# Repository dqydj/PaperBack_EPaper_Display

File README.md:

# PaperBack EPaper Display

PaperBack is a modular, internet connected _*OR*_ VGA EPaper Display. It consists of a breakout board for a 39 pin ePaper display and an ESP32 in one mode. In the other, remove the ESP32 and attach a VGA Conversion board and use regular VGA input to drive the display!

PaperBack is an entry in the 2017 Hackaday Prize, you can see a more complete (and verbose!) [writeup here](https://hackaday.io/project/21607-paperback-desktop-e-paper-monitor).

## Hardware Overview

Currently, PaperBack works both driven by an ESP32 Development Board, or directly via VGA with the attached second PCB.

Hardware Overview:

* Espressif ESP32 Dev Board
* ED060SC4 // LB060S01 // LB060S04 6" ePaper Display
* 800x600 Resolution
* 16 Color (Greyscale) Support / 4-Bit Grey

## Software/Firmware Overview

Remember, choose one at a time! You can use the ESP32 breakout board with the ESP32 dev board, or remove the dev board and attach the VGA converter.

### VGA Driven

Unplug any ESP32 from the socket and attach both boards, then attach power (see below). When the board detects a signal it will start to refresh.

All firmware is in the /firmware_VGA/FPGA and /firmware_VGA/Microcontroller directories.

The user switches change color depth (read: shades of gray. 2 color is black & white.) and refresh speed:
Switch 3 (Furthest from Microcontroller)
Switch 2
Switch 1 (Closest to Microcontroller)

* On  On  On  - 16 color, ~10 seconds between frames
* On  On  Off - 16 color, ~5 seconds between frames
* On  Off On  - 4 color, ~10 seconds between frames
* On  Off Off - 4 color, ~5 seconds between frames
* Off On  On  - 4 color, ~1 frame per second
* Off On  Off - 2 color, ~10 seconds between frames
* Off Off On  - 2 color, ~5 seconds between frames
* Off Off Off - 2 color, ~1 frame per second

### ESP32 Dev Board Driven

Remove the second PCB if attached, then add the ESP32. There are *easy* ways to add power (there are pins exposed too, but these are easiest). Unless using Lithium and the DC adapter, only use one at a time!
* The board supports a single cell lithium ion battery with JST connector, and can charge it through the DC adapter hookup. Polarity is marker.
* The board can take a 2.1mm jack DC adapter, center positive. Aim for between 4.8 and 7 volts (don't create too much heat with something more).
* Disconnect all other supplies if you do this, but you can power it over USB from the ESP32. Connect the jumper labeled 'JP2' for this option.

Demos:

1. The Python utility `convert.py` in `/software/image_converter` automatically converts images which are compatible with Paperback's basic image demo. The image demo is in /firmware_ESP32/Paperback_Greyscale_Static_Image.

## Licensing and Other

* My main site: [DQYDJ](https://dqydj.com)
* Where available, all of the code is licensed as MIT.
* Where available, all of the hardware is licensed as MIT.
* If needed, other licenses will be quoted for individual parts.
* I would, of course, _love_ a link if you use any assets - but feel free to use everything as you wish.

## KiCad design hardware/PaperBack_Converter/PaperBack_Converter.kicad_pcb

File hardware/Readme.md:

# Hardware Directory

Here you'll find the files you will need to reproduce Paperback.  There are two boards:

* *PaperBack_Display* The Display breakout board.  Can take an ESP32 Development Kit and run the display without the Video converter board.
* *PaperBack_Converter* The VGA conversion board.  Takes VGA, captures a frame, puts it in memory, then outputs to the ePaper screen.  _You can't run the ESP32 if you choose to dock board 2! Do not insert it!_.  

## Editing the Files

All files are from KiCad, although Gerbers are a universal format.  I've also included the PDF schematics as well if you'd like to spin a new PCB from scratch.

## License

MIT

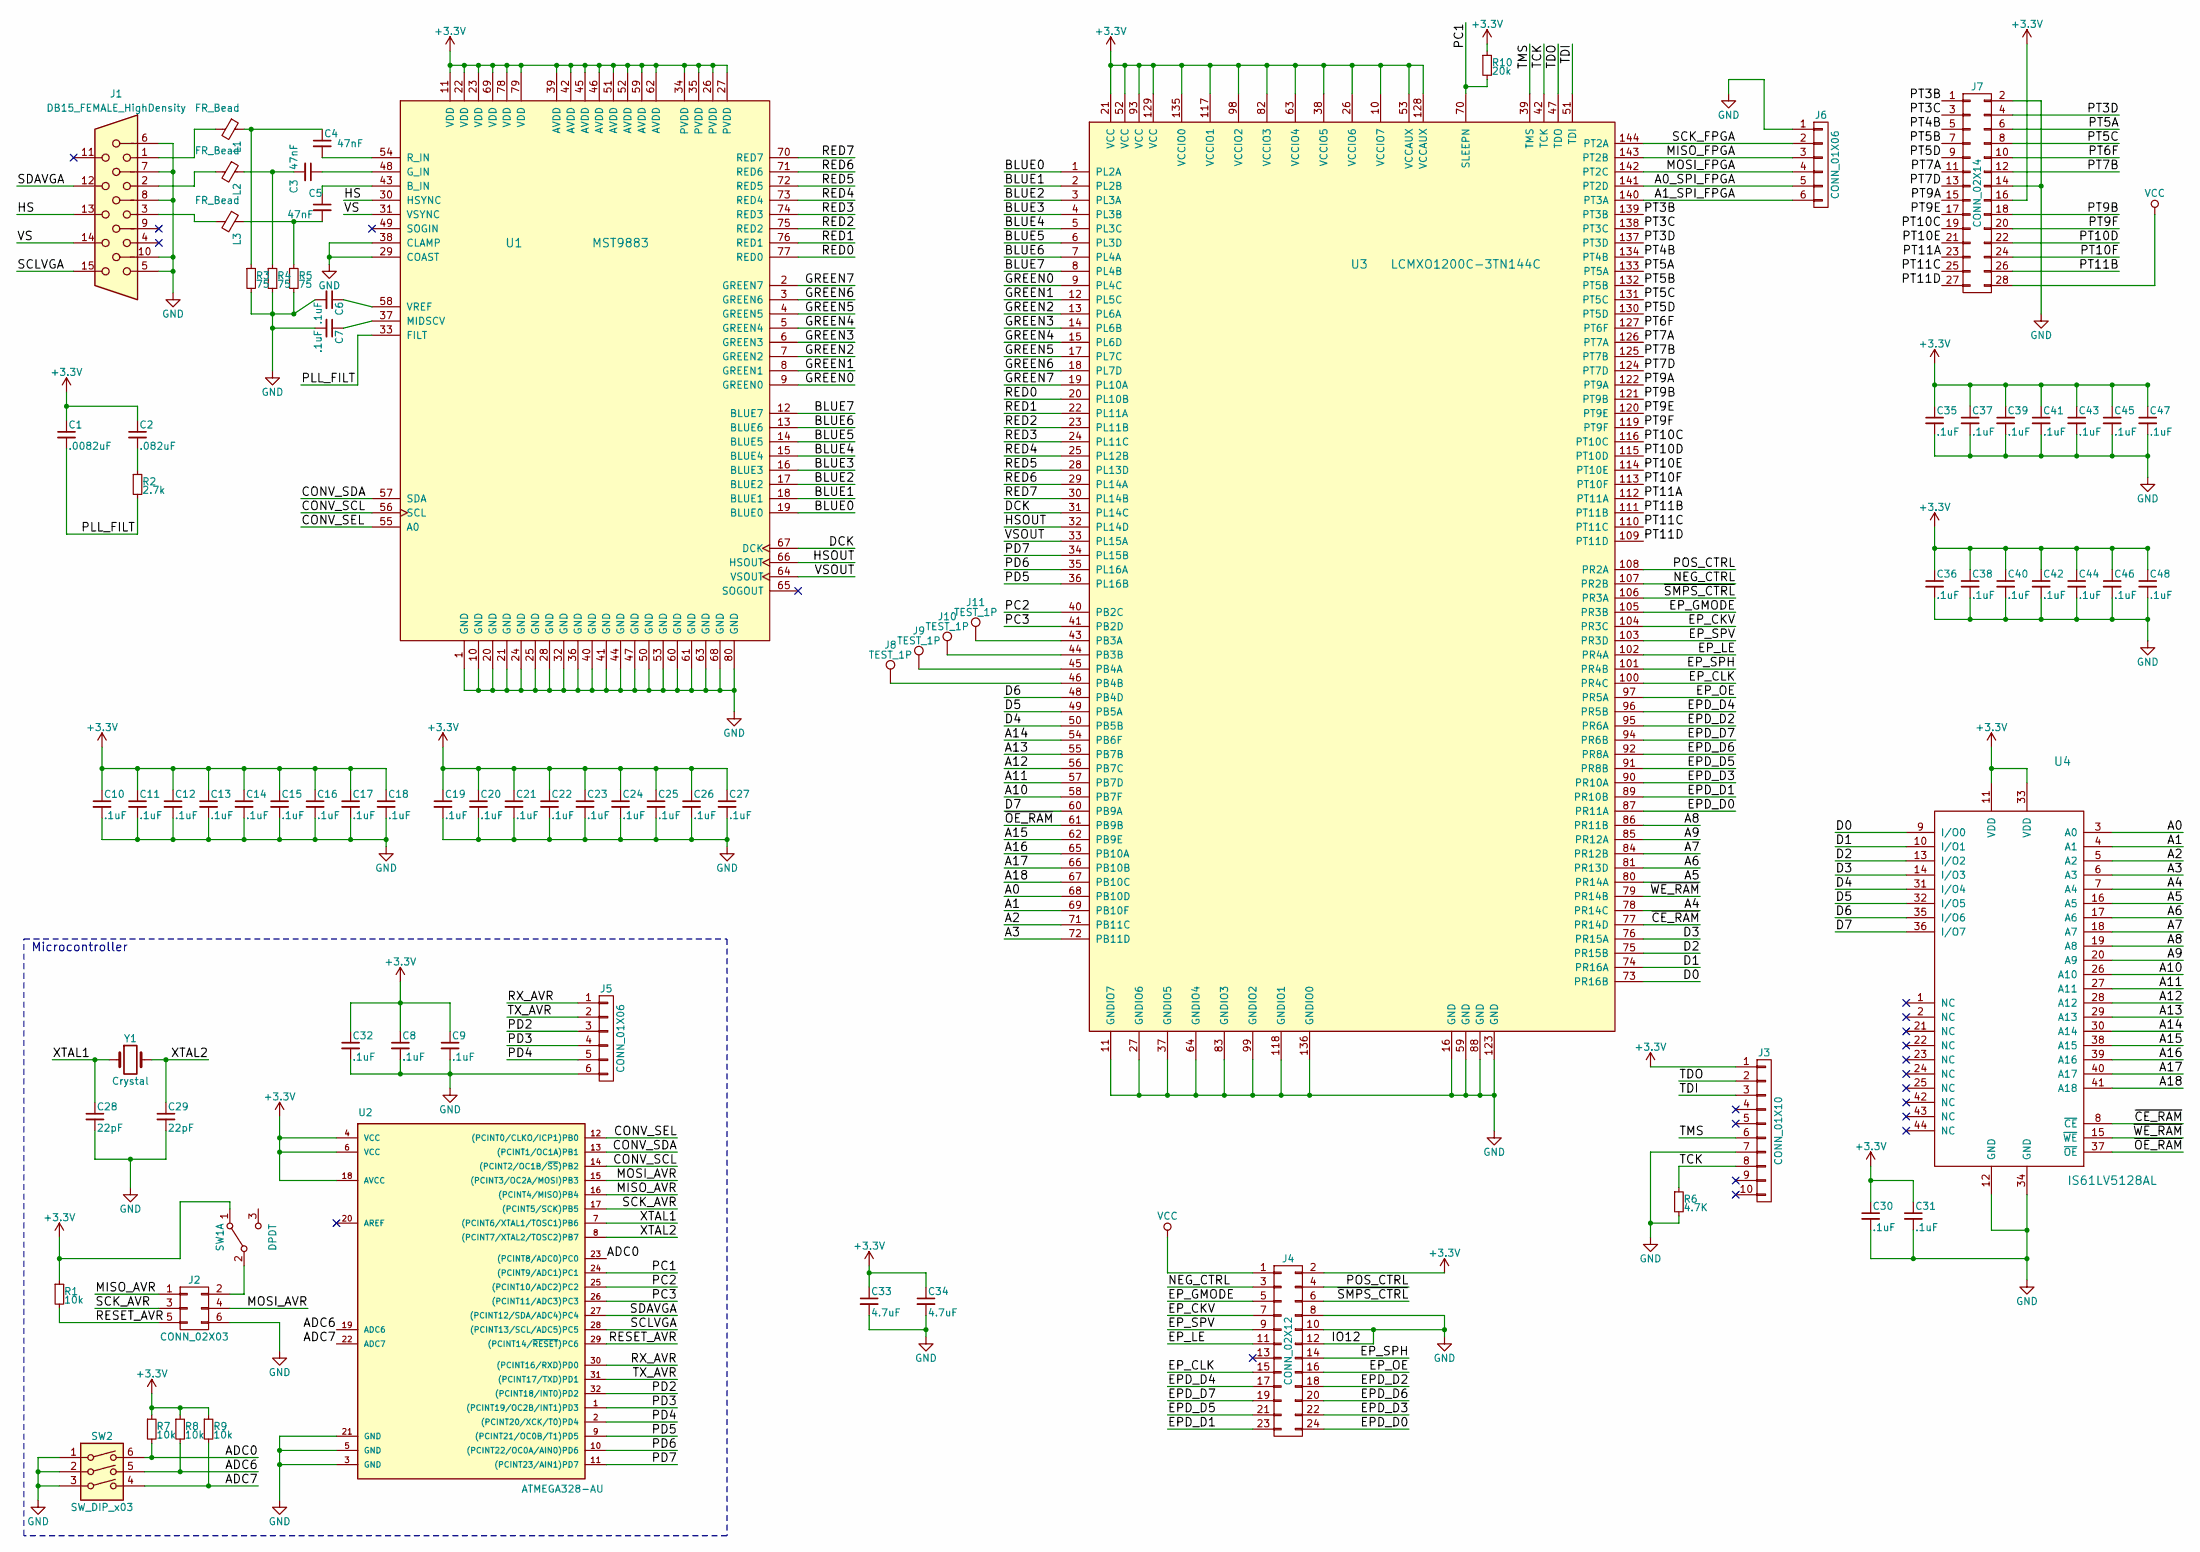
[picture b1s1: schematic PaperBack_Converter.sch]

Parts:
C1: .0082uF; C_0603_HandSoldering
C2: .082uF; C_0603_HandSoldering
C3, C4, C5: 47nF; C_0603_HandSoldering
C6, C7, C8, C9, C10, C11, C12, C13, C14, C15, C16, C17, C18, C19, C20, C21, C22, C23, C24, C25, C26, C27, C30, C31, C32, C35, C36, C37, C38, C39, C40, C41, C42, C43, C44, C45, C46, C47, C48: .1uF; C_0603_HandSoldering
C28, C29: 22pF; C_0603_HandSoldering
C33, C34: 4.7uF; C_0603_HandSoldering
J1: DB15_FEMALE_HighDensity; VGA_HD15
J2: CONN_02X03; Pin_Header_Straight_2x03_Pitch2.54mm
J3: CONN_01X10; Pin_Header_Straight_1x10_Pitch2.54mm
J4: CONN_02X12; Pin_Header_Straight_2x12_Pitch2.54mm
J5, J6: CONN_01X06; Pin_Header_Straight_1x06_Pitch2.54mm
J7: CONN_02X14; Socket_Strip_Straight_2x14_Pitch2.54mm
J8, J9, J10, J11: TEST_1P; Measurement_Point_Round-SMD-Pad_Small
L1, L2, L3: FR_Bead; L_0805_HandSoldering
R1, R7, R8, R9: 10k; R_0805_HandSoldering
R2: 2.7k; R_0805_HandSoldering
R3, R4, R5: 75; R_0805_HandSoldering
R6: 4.7K; R_0805_HandSoldering
R10: 20k; R_0805_HandSoldering
SW1: DPDT; Pin_Header_Straight_1x03_Pitch2.54mm
SW2: SW_DIP_x03; SW_DIP_x3_W7.62mm_Slide
U1: MST9883; TQFP-80_14x14mm_Pitch0.65mm
U2: ATMEGA328-AU; TQFP-32_7x7mm_Pitch0.8mm
U3: LCMXO1200C-3TN144C; TQFP-144_20x20mm_Pitch0.5mm
U4: IS61LV5128AL; TSOP_II_44_0.8mm
Y1: Crystal; Crystal_SMD_HC49-SD

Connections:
+3V3: C1.1, C2.1, C8.1, C9.1, C10.1, C11.1, C12.1, C13.1, C14.1, C15.1, C16.1, C17.1, C18.1, C19.1, C20.1, C21.1, C22.1, C23.1, C24.1, C25.1, C26.1, C27.1, C30.1, C31.1, C32.1, C33.1, C34.1, C35.1, C36.1, C37.1, C38.1, C39.1, C40.1, C41.1, C42.1, C43.1, C44.1, C45.1, C46.1, C47.1, C48.1, J3.1, J4.2, J7.16, R1.1, R7.1, R8.1, R9.1, R10.1, SW1.1 (A), U1.11 (VDD), U1.22 (VDD), U1.23 (VDD), U1.26 (PVDD), U1.27 (PVDD), U1.34 (PVDD), U1.35 (PVDD), U1.39 (AVDD), U1.42 (AVDD), U1.45 (AVDD), U1.46 (AVDD), U1.51 (AVDD), U1.52 (AVDD), U1.59 (AVDD), U1.62 (AVDD), U1.69 (VDD), U1.78 (VDD), U1.79 (VDD), U2.4 (VCC), U2.6 (VCC), U2.18 (AVCC), U3.10 (VCCIO7), U3.21 (VCC), U3.26 (VCCIO6), U3.38 (VCCIO5), U3.52 (VCC), U3.53 (VCCAUX), U3.63 (VCCIO4), U3.82 (VCCIO3), U3.93 (VCC), U3.98 (VCCIO2), U3.117 (VCCIO1), U3.128 (VCCAUX), U3.129 (VCC), U3.135 (VCCIO0), U4.11 (VDD), U4.33 (VDD)
/A0: U3.68 (PB10D), U4.3 (A0)
/A0_SPI_FPGA: J6.5, U3.141 (PT2D)
/A1: U3.69 (PB10F), U4.4 (A1)
/A1_SPI_FPGA: J6.6, U3.140 (PT3A)
/A2: U3.71 (PB11C), U4.5 (A2)
/A3: U3.72 (PB11D), U4.6 (A3)
/A4: U3.78 (PR14C), U4.7 (A4)
/A5: U3.80 (PR14A), U4.16 (A5)
/A6: U3.81 (PR13D), U4.17 (A6)
/A7: U3.84 (PR12B), U4.18 (A7)
/A8: U3.86 (PR11B), U4.19 (A8)
/A9: U3.85 (PR12A), U4.20 (A9)
/A10: U3.58 (PB7F), U4.26 (A10)
/A11: U3.57 (PB7D), U4.27 (A11)
/A12: U3.56 (PB7C), U4.28 (A12)
/A13: U3.55 (PB7B), U4.29 (A13)
/A14: U3.54 (PB6F), U4.30 (A14)
/A15: U3.62 (PB9E), U4.38 (A15)
/A16: U3.65 (PB10A), U4.39 (A16)
/A17: U3.66 (PB10B), U4.40 (A17)
/A18: U3.67 (PB10C), U4.41 (A18)
/ADC0: R7.2, SW2.6, U2.23 ((PCINT8/ADC0)PC0)
/ADC6: R8.2, SW2.5, U2.19 (ADC6)
/ADC7: R9.2, SW2.4, U2.22 (ADC7)
/BLUE0: U1.19 (BLUE0), U3.1 (PL2A)
/BLUE1: U1.18 (BLUE1), U3.2 (PL2B)
/BLUE2: U1.17 (BLUE2), U3.3 (PL3A)
/BLUE3: U1.16 (BLUE3), U3.4 (PL3B)
/BLUE4: U1.15 (BLUE4), U3.5 (PL3C)
/BLUE5: U1.14 (BLUE5), U3.6 (PL3D)
/BLUE6: U1.13 (BLUE6), U3.7 (PL4A)
/BLUE7: U1.12 (BLUE7), U3.8 (PL4B)
/CONV_SCL: U1.56 (SCL), U2.14 ((PCINT2/OC1B/~SS~)PB2)
/CONV_SDA: U1.57 (SDA), U2.13 ((PCINT1/OC1A)PB1)
/CONV_SEL: U1.55 (A0), U2.12 ((PCINT0/CLKO/ICP1)PB0)
/D0: U3.73 (PR16B), U4.9 (I/O0)
/D1: U3.74 (PR16A), U4.10 (I/O1)
/D2: U3.75 (PR15B), U4.13 (I/O2)
/D3: U3.76 (PR15A), U4.14 (I/O3)
/D4: U3.50 (PB5B), U4.31 (I/O4)
/D5: U3.49 (PB5A), U4.32 (I/O5)
/D6: U3.48 (PB4D), U4.35 (I/O6)
/D7: U3.60 (PB9A), U4.36 (I/O7)
/DCK: U1.67 (DCK), U3.31 (PL14C)
/EPD_D0: J4.24, U3.87 (PR11A)
/EPD_D1: J4.23, U3.89 (PR10B)
/EPD_D2: J4.18, U3.95 (PR6A)
/EPD_D3: J4.22, U3.90 (PR10A)
/EPD_D4: J4.17, U3.96 (PR5B)
/EPD_D5: J4.21, U3.91 (PR8B)
/EPD_D6: J4.20, U3.92 (PR8A)
/EPD_D7: J4.19, U3.94 (PR6B)
/EP_CKV: J4.7, U3.104 (PR3C)
/EP_CLK: J4.15, U3.100 (PR4C)
/EP_GMODE: J4.5, U3.105 (PR3B)
/EP_LE: J4.11, U3.102 (PR4A)
/EP_OE: J4.16, U3.97 (PR5A)
/EP_SPH: J4.14, U3.101 (PR4B)
/EP_SPV: J4.9, U3.103 (PR3D)
/GREEN0: U1.9 (GREEN0), U3.9 (PL4C)
/GREEN1: U1.8 (GREEN1), U3.12 (PL5C)
/GREEN2: U1.7 (GREEN2), U3.13 (PL6A)
/GREEN3: U1.6 (GREEN3), U3.14 (PL6B)
/GREEN4: U1.5 (GREEN4), U3.15 (PL6D)
/GREEN5: U1.4 (GREEN5), U3.17 (PL7C)
/GREEN6: U1.3 (GREEN6), U3.18 (PL7D)
/GREEN7: U1.2 (GREEN7), U3.19 (PL10A)
/HS: J1.13, U1.30 (HSYNC)
/HSOUT: U1.66 (HSOUT), U3.32 (PL14D)
/MISO_AVR: J2.1, U2.16 ((PCINT4/MISO)PB4)
/MISO_FPGA: J6.3, U3.143 (PT2B)
/MOSI_AVR: J2.4, U2.15 ((PCINT3/OC2A/MOSI)PB3)
/MOSI_FPGA: J6.4, U3.142 (PT2C)
/NEG_CTRL: J4.3, U3.107 (PR2B)
/PC1: R10.2, U2.24 ((PCINT9/ADC1)PC1), U3.70 (SLEEPN)
/PC2: U2.25 ((PCINT10/ADC2)PC2), U3.40 (PB2C)
/PC3: U2.26 ((PCINT11/ADC3)PC3), U3.41 (PB2D)
/PD2: J5.3, U2.32 ((PCINT18/INT0)PD2)
/PD3: J5.4, U2.1 ((PCINT19/OC2B/INT1)PD3)
/PD4: J5.5, U2.2 ((PCINT20/XCK/T0)PD4)
/PD5: U2.9 ((PCINT21/OC0B/T1)PD5), U3.36 (PL16B)
/PD6: U2.10 ((PCINT22/OC0A/AIN0)PD6), U3.35 (PL16A)
/PD7: U2.11 ((PCINT23/AIN1)PD7), U3.34 (PL15B)
/PLL_FILT: C1.2, R2.2, U1.33 (FILT)
/POS_CTRL: J4.4, U3.108 (PR2A)
/PT3B: J7.1, U3.139 (PT3B)
/PT3C: J7.3, U3.138 (PT3C)
/PT3D: J7.4, U3.137 (PT3D)
/PT4B: J7.5, U3.134 (PT4B)
/PT5A: J7.6, U3.133 (PT5A)
/PT5B: J7.7, U3.132 (PT5B)
/PT5C: J7.8, U3.131 (PT5C)
/PT5D: J7.9, U3.130 (PT5D)
/PT6F: J7.10, U3.127 (PT6F)
/PT7A: J7.11, U3.126 (PT7A)
/PT7B: J7.12, U3.125 (PT7B)
/PT7D: J7.13, U3.124 (PT7D)
/PT9A: J7.15, U3.122 (PT9A)
/PT9B: J7.18, U3.121 (PT9B)
/PT9E: J7.17, U3.120 (PT9E)
/PT9F: J7.20, U3.119 (PT9F)
/PT10C: J7.19, U3.116 (PT10C)
/PT10D: J7.22, U3.115 (PT10D)
/PT10E: J7.21, U3.114 (PT10E)
/PT10F: J7.24, U3.113 (PT10F)
/PT11A: J7.23, U3.112 (PT11A)
/PT11B: J7.26, U3.111 (PT11B)
/PT11C: J7.25, U3.110 (PT11C)
/PT11D: J7.27, U3.109 (PT11D)
/RED0: U1.77 (RED0), U3.20 (PL10B)
/RED1: U1.76 (RED1), U3.22 (PL11A)
/RED2: U1.75 (RED2), U3.23 (PL11B)
/RED3: U1.74 (RED3), U3.24 (PL11C)
/RED4: U1.73 (RED4), U3.25 (PL12B)
/RED5: U1.72 (RED5), U3.28 (PL13D)
/RED6: U1.71 (RED6), U3.29 (PL14A)
/RED7: U1.70 (RED7), U3.30 (PL14B)
/RESET_AVR: J2.5, R1.2, U2.29 ((PCINT14/~RESET~)PC6)
/RX_AVR: J5.1, U2.30 ((PCINT16/RXD)PD0)
/SCK_AVR: J2.3, U2.17 ((PCINT5/SCK)PB5)
/SCK_FPGA: J6.2, U3.144 (PT2A)
/SCLVGA: J1.15, U2.28 ((PCINT13/SCL/ADC5)PC5)
/SDAVGA: J1.12, U2.27 ((PCINT12/SDA/ADC4)PC4)
/TCK: J3.8, R6.1, U3.42 (TCK)
/TDI: J3.3, U3.51 (TDI)
/TDO: J3.2, U3.47 (TDO)
/TMS: J3.6, U3.39 (TMS)
/TX_AVR: J5.2, U2.31 ((PCINT17/TXD)PD1)
/VS: J1.14, U1.31 (VSYNC)
/VSOUT: U1.64 (VSOUT), U3.33 (PL15A)
/XTAL1: C28.1, U2.7 ((PCINT6/XTAL1/TOSC1)PB6), Y1.1
/XTAL2: C29.1, U2.8 ((PCINT7/XTAL2/TOSC2)PB7), Y1.2
/~CE_RAM: U3.77 (PR14D), U4.8 (~CE)
/~OE_RAM: U3.61 (PB9B), U4.37 (~OE)
/~SMPS_CTRL: J4.6, U3.106 (PR3A)
/~WE_RAM: U3.79 (PR14B), U4.15 (~WE)
GND: C6.2, C7.2, C8.2, C9.2, C10.2, C11.2, C12.2, C13.2, C14.2, C15.2, C16.2, C17.2, C18.2, C19.2, C20.2, C21.2, C22.2, C23.2, C24.2, C25.2, C26.2, C27.2, C28.2, C29.2, C30.2, C31.2, C32.2, C33.2, C34.2, C35.2, C36.2, C37.2, C38.2, C39.2, C40.2, C41.2, C42.2, C43.2, C44.2, C45.2, C46.2, C47.2, C48.2, J1.5, J1.6, J1.7, J1.8, J1.10, J2.6, J3.7, J4.8, J4.10, J4.12, J5.6, J6.1, J7.2, J7.14, R3.2, R4.2, R5.2, R6.2, SW2.1, SW2.2, SW2.3, U1.1 (GND), U1.10 (GND), U1.20 (GND), U1.21 (GND), U1.24 (GND), U1.25 (GND), U1.28 (GND), U1.29 (COAST), U1.32 (GND), U1.36 (GND), U1.38 (CLAMP), U1.40 (GND), U1.41 (GND), U1.44 (GND), U1.47 (GND), U1.50 (GND), U1.53 (GND), U1.60 (GND), U1.61 (GND), U1.63 (GND), U1.68 (GND), U1.80 (GND), U2.3 (GND), U2.5 (GND), U2.21 (GND), U3.11 (GNDIO7), U3.16 (GND), U3.27 (GNDIO6), U3.37 (GNDIO5), U3.59 (GND), U3.64 (GNDIO4), U3.83 (GNDIO3), U3.88 (GND), U3.99 (GNDIO2), U3.118 (GNDIO1), U3.123 (GND), U3.136 (GNDIO0), U4.12 (GND), U4.34 (GND)
unnamed: C2.2, R2.1
unnamed: C3.1, U1.48 (G_IN)
unnamed: C3.2, L2.1, R4.1
unnamed: C4.1, L1.1, R3.1
unnamed: C4.2, U1.54 (R_IN)
unnamed: C5.1, U1.43 (B_IN)
unnamed: C5.2, L3.1, R5.1
unnamed: C6.1, U1.58 (VREF)
unnamed: C7.1, U1.37 (MIDSCV)
unnamed: J1.1, L1.2
unnamed: J1.2, L2.2
unnamed: J1.3, L3.2
unnamed: J2.2, SW1.2 (B)
unnamed: J8.1, U3.46 (PB4B)
unnamed: J9.1, U3.45 (PB4A)
unnamed: J10.1, U3.44 (PB3B)
unnamed: J11.1, U3.43 (PB3A)
VCC: J4.1, J7.28

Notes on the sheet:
Microcontroller

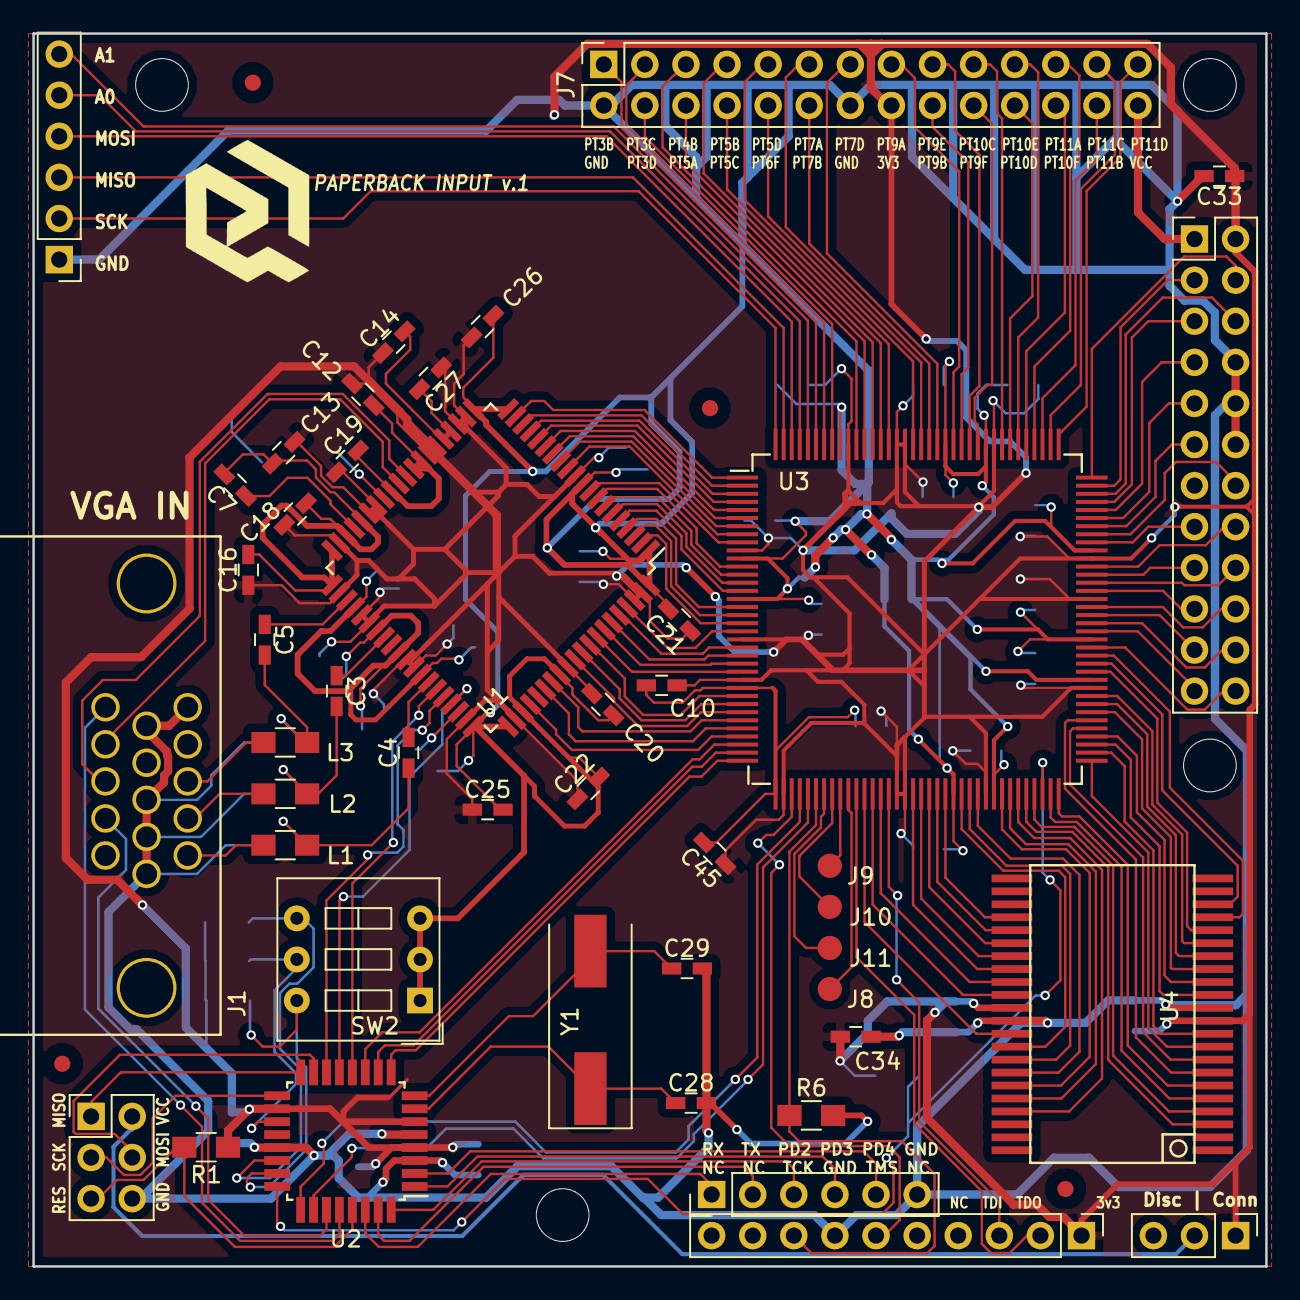
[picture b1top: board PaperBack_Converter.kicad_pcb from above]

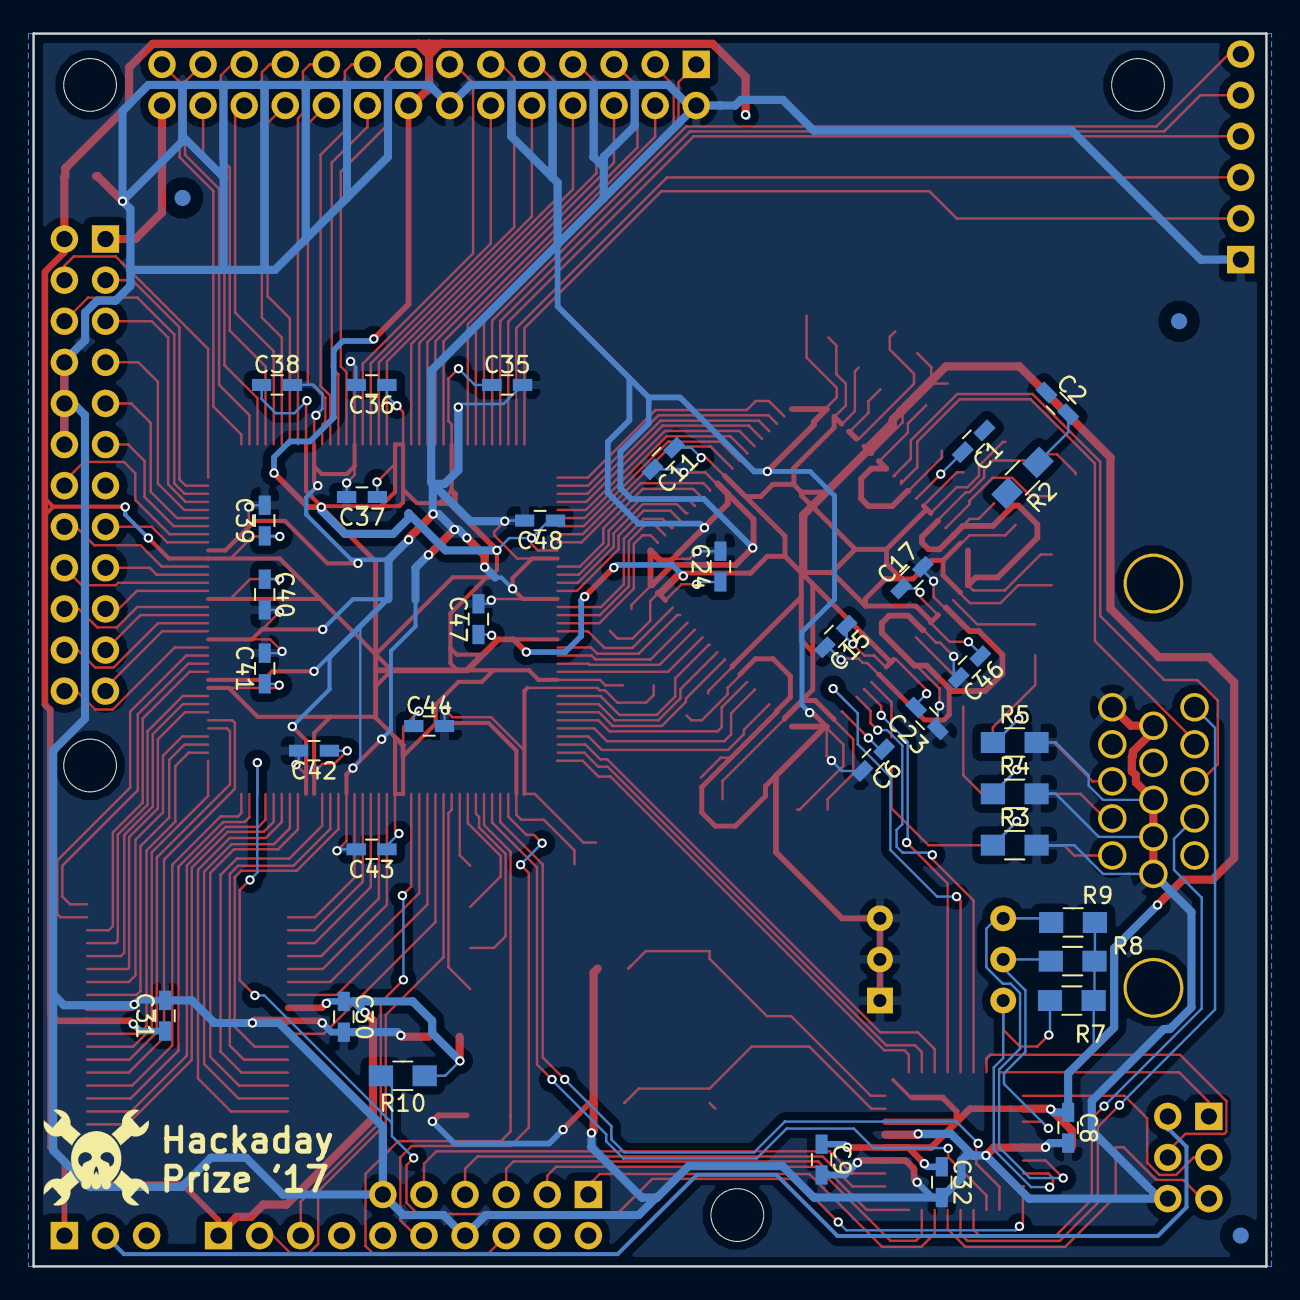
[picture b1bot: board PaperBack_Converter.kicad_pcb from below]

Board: 2 copper layers, 76.2 x 76.2 mm, 79 parts (34 on the bottom side), 156 nets.

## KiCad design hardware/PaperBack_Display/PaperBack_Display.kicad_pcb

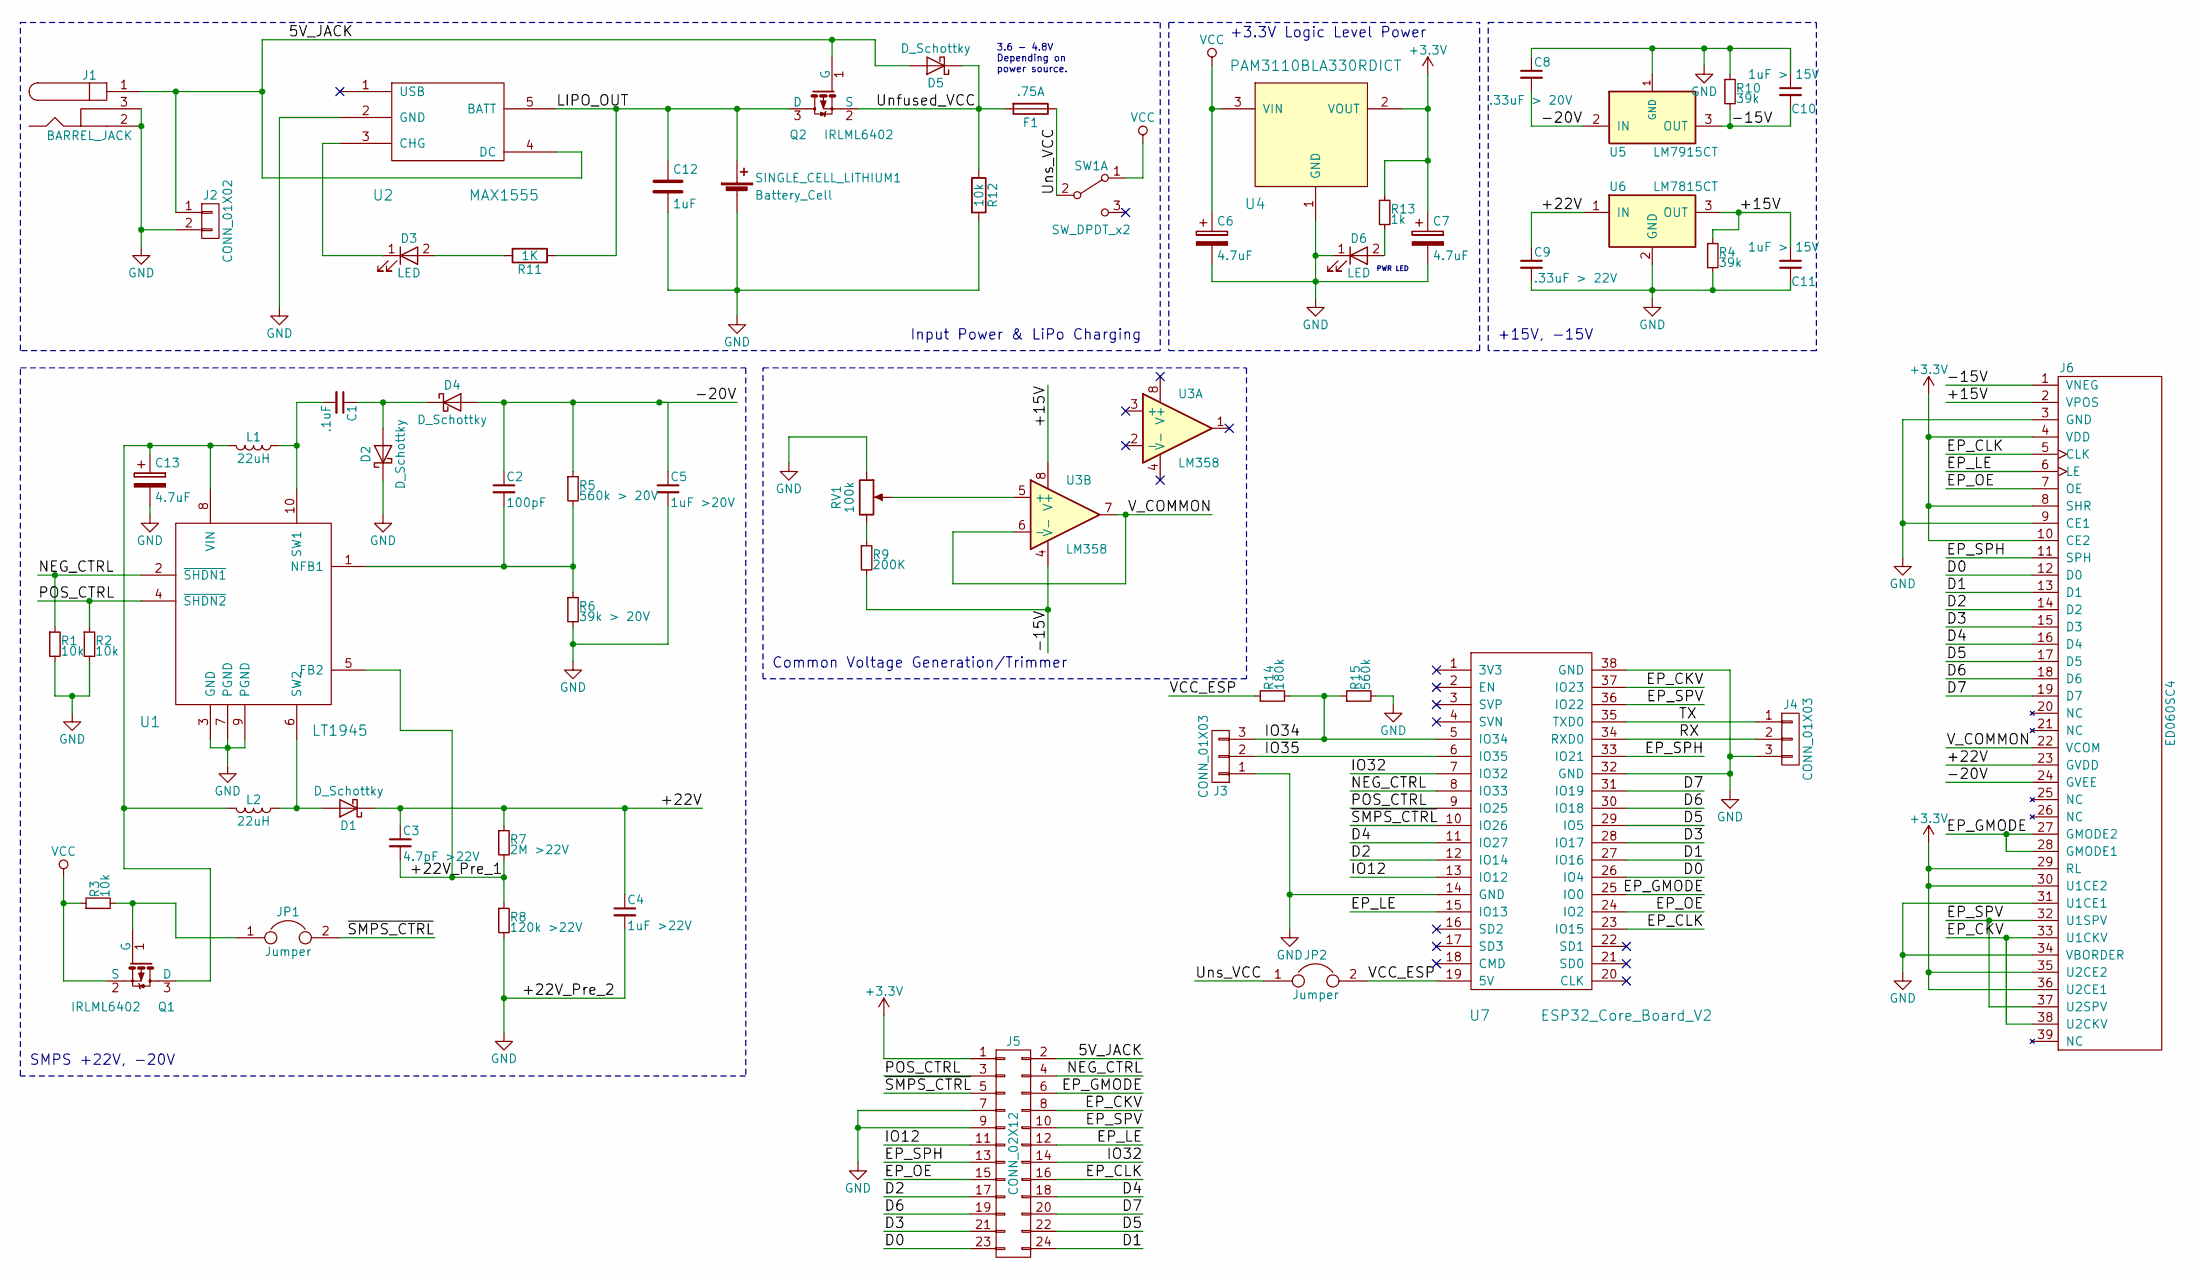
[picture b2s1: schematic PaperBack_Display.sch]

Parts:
C1: .1uF; C_0603_HandSoldering
C2: 100pF; C_0603_HandSoldering
C3: 4.7pF >22V; C_0603_HandSoldering
C4: 1uF >22V; C_0603_HandSoldering
C5: 1uF >20V; C_0603_HandSoldering
C6, C7, C13: 4.7uF; C_0603_HandSoldering
C8: .33uF > 20V; C_0603_HandSoldering
C9: .33uF > 22V; C_0603_HandSoldering
C10, C11: 1uF > 15V; C_0603_HandSoldering
C12: 1uF; C_0603_HandSoldering
D1, D2, D4, D5: D_Schottky; D_SOD-123F
D3, D6: LED; LED_0805
F1: .75A; R_1210_HandSoldering
J1: BARREL_JACK; Switchcraft_5.5_2.1_Barrel_Jack
J2: CONN_01X02; Pin_Header_Straight_1x02_Pitch2.54mm
J3, J4: CONN_01X03; Pin_Header_Straight_1x03_Pitch2.54mm
J5: CONN_02X12; Pin_Header_Straight_2x12_Pitch2.54mm
J6: ED060SC4
JP1, JP2: Jumper; Pin_Header_Straight_1x02_Pitch2.54mm
L1, L2: 22uH; DG6050C_Murata_Inductor
Q1, Q2: IRLML6402; SOT-23
R1, R2, R3, R12: 10k; R_0805_HandSoldering
R4, R10: 39k; R_0805_HandSoldering
R5: 560k > 20V; R_0805_HandSoldering
R6: 39k > 20V; R_0805_HandSoldering
R7: 2M >22V; R_0805_HandSoldering
R8: 120k >22V; R_0805_HandSoldering
R9: 200K; R_0805_HandSoldering
R11: 1K; R_0805_HandSoldering
R13: 1k; R_0805_HandSoldering
R14: 180k; R_0805_HandSoldering
R15: 560k; R_0805_HandSoldering
RV1: 100k; CB10V_Trimmer
SINGLE_CELL_LITHIUM1: Battery_Cell; JST_Right_Angle_02x01
SW1: SW_DPDT_x2; Pin_Header_Straight_1x03_Pitch2.54mm
U1: LT1945; MSOP-10_3x3mm_Pitch0.5mm
U2: MAX1555; SOT-23-5_HandSoldering
U3: LM358; DIP-8_W7.62mm
U4: PAM3110BLA330RDICT; TO-252-3_TabPin2
U5: LM7915CT; TO-252-3_TabPin2
U6: LM7815CT; TO-252-3_TabPin2
U7: ESP32_Core_Board_V2; ESP32_Core_Board_v2

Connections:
+3V3: C7.1, J5.1, J6.4 (VDD), J6.8 (SHR), J6.10 (CE2), J6.29 (RL), J6.30 (U1CE2), J6.35 (U2CE2), J6.36 (U2CE1), R13.1, U4.2 (VOUT)
/5V_JACK: D5.2 (A), J1.1, J2.1, J5.2, Q2.1 (G), U2.4 (DC)
/+15V: C11.1, J6.2 (VPOS), R4.1, U3.8 (V+), U6.3 (OUT)
/+22V: C3.1, C4.1, C9.1, D1.1 (K), J6.23 (GVDD), R7.1, U6.1 (IN)
/+22V_Pre_1: C3.2, R7.2, R8.1, U1.5 (FB2)
/-15V: C10.2, J6.1 (VNEG), R9.2, R10.2, U3.4 (V-), U5.3 (OUT)
/-20V: C2.1, C5.1, C8.2, D4.2 (A), J6.24 (GVEE), R5.1, U5.2 (IN)
/D0: J5.23, J6.12 (D0), U7.26 (IO4)
/D1: J5.24, J6.13 (D1), U7.27 (IO16)
/D2: J5.17, J6.14 (D2), U7.12 (IO14)
/D3: J5.21, J6.15 (D3), U7.28 (IO17)
/D4: J5.18, J6.16 (D4), U7.11 (IO27)
/D5: J5.22, J6.17 (D5), U7.29 (IO5)
/D6: J5.19, J6.18 (D6), U7.30 (IO18)
/D7: J5.20, J6.19 (D7), U7.31 (IO19)
/EP_CKV: J5.8, J6.33 (U1CKV), J6.38 (U2CKV), U7.37 (IO23)
/EP_CLK: J5.16, J6.5 (CLK), U7.23 (IO15)
/EP_GMODE: J5.6, J6.27 (GMODE2), J6.28 (GMODE1), U7.25 (IO0)
/EP_LE: J5.12, J6.6 (LE), U7.15 (IO13)
/EP_OE: J5.15, J6.7 (OE), U7.24 (IO2)
/EP_SPH: J5.13, J6.11 (SPH), U7.33 (IO21)
/EP_SPV: J5.10, J6.32 (U1SPV), J6.37 (U2SPV), U7.36 (IO22)
/IO12: J5.11, U7.13 (IO12)
/IO32: J5.14, U7.7 (IO32)
/IO34: J3.3, R14.2, R15.1, U7.5 (IO34)
/IO35: J3.2, U7.6 (IO35)
/LIPO_OUT: C12.1, Q2.3 (D), R11.1, SINGLE_CELL_LITHIUM1.1 (+), U2.5 (BATT)
/NEG_CTRL: J5.4, R1.1, U1.2 (~SHDN1), U7.8 (IO33)
/POS_CTRL: J5.3, R2.1, U1.4 (~SHDN2), U7.9 (IO25)
/RX: J4.2, U7.34 (RXD0)
/TX: J4.1, U7.35 (TXD0)
/Unfused_VCC: D5.1 (K), F1.2, Q2.2 (S), R12.1
/Uns_VCC: F1.1, JP2.1, SW1.2 (B)
/VCC_ESP: JP2.2, R14.1, U7.19 (5V)
/V_COMMON: J6.22 (VCOM), U3.6 (-), U3.7
/~SMPS_CTRL: J5.5, JP1.2, U7.10 (IO26)
GND: C4.2, C5.2, C6.2, C7.2, C8.1, C9.2, C10.1, C11.2, C12.2, C13.2, D2.1 (K), D6.1 (K), J1.2, J1.3, J2.2, J3.1, J4.3, J5.7, J5.9, J6.3 (GND), J6.9 (CE1), J6.31 (U1CE1), J6.34 (VBORDER), R1.2, R2.2, R4.2, R6.2, R8.2, R10.1, R12.2, R15.2, RV1.1, SINGLE_CELL_LITHIUM1.2 (-), U1.3 (GND), U1.7 (PGND), U1.9 (PGND), U2.2 (GND), U4.1 (GND), U5.1 (GND), U6.2 (GND), U7.14 (GND), U7.32 (GND), U7.38 (GND)
unnamed: C1.1, D2.2 (A), D4.1 (K)
unnamed: C1.2, L1.1, U1.10 (SW1)
unnamed: C2.2, R5.2, R6.1, U1.1 (NFB1)
unnamed: C13.1, L1.2, L2.2, Q1.3 (D), U1.8 (VIN)
unnamed: D1.2 (A), L2.1, U1.6 (SW2)
unnamed: D3.1 (K), U2.3 (CHG)
unnamed: D3.2 (A), R11.2
unnamed: D6.2 (A), R13.2
unnamed: JP1.1, Q1.1 (G), R3.2
unnamed: R9.1, RV1.3
unnamed: RV1.2, U3.5 (+)
VCC: C6.1, Q1.2 (S), R3.1, SW1.1 (A), U4.3 (VIN)

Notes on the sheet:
3.6 - 4.8V Depending on power source.
Input Power & LiPo Charging
+3.3V Logic Level Power
SMPS +22V, -20V
+15V, -15V
Common Voltage Generation/Trimmer
PWR LED

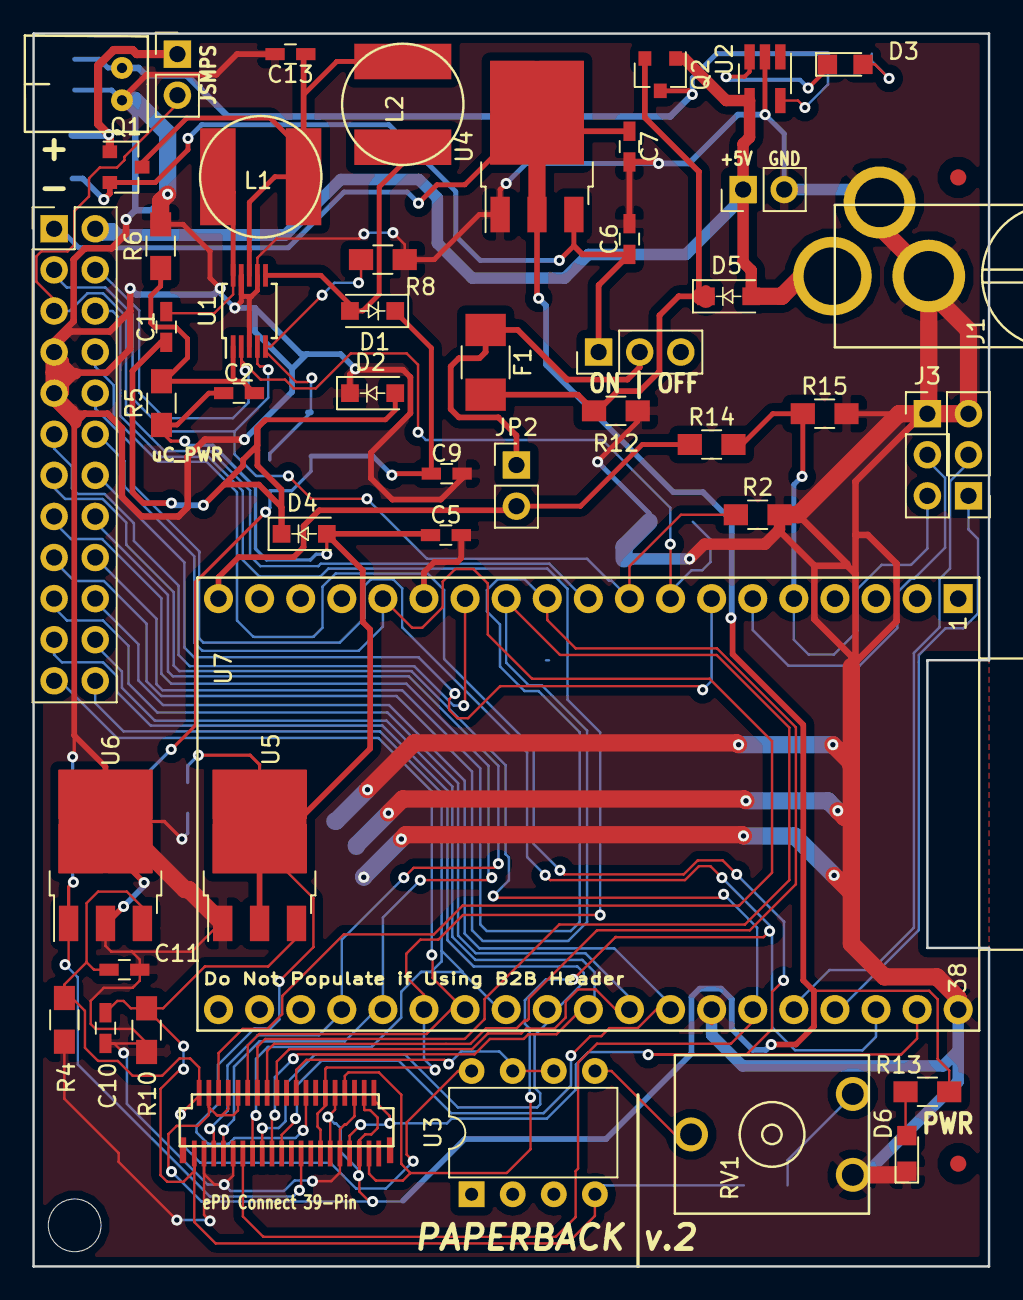
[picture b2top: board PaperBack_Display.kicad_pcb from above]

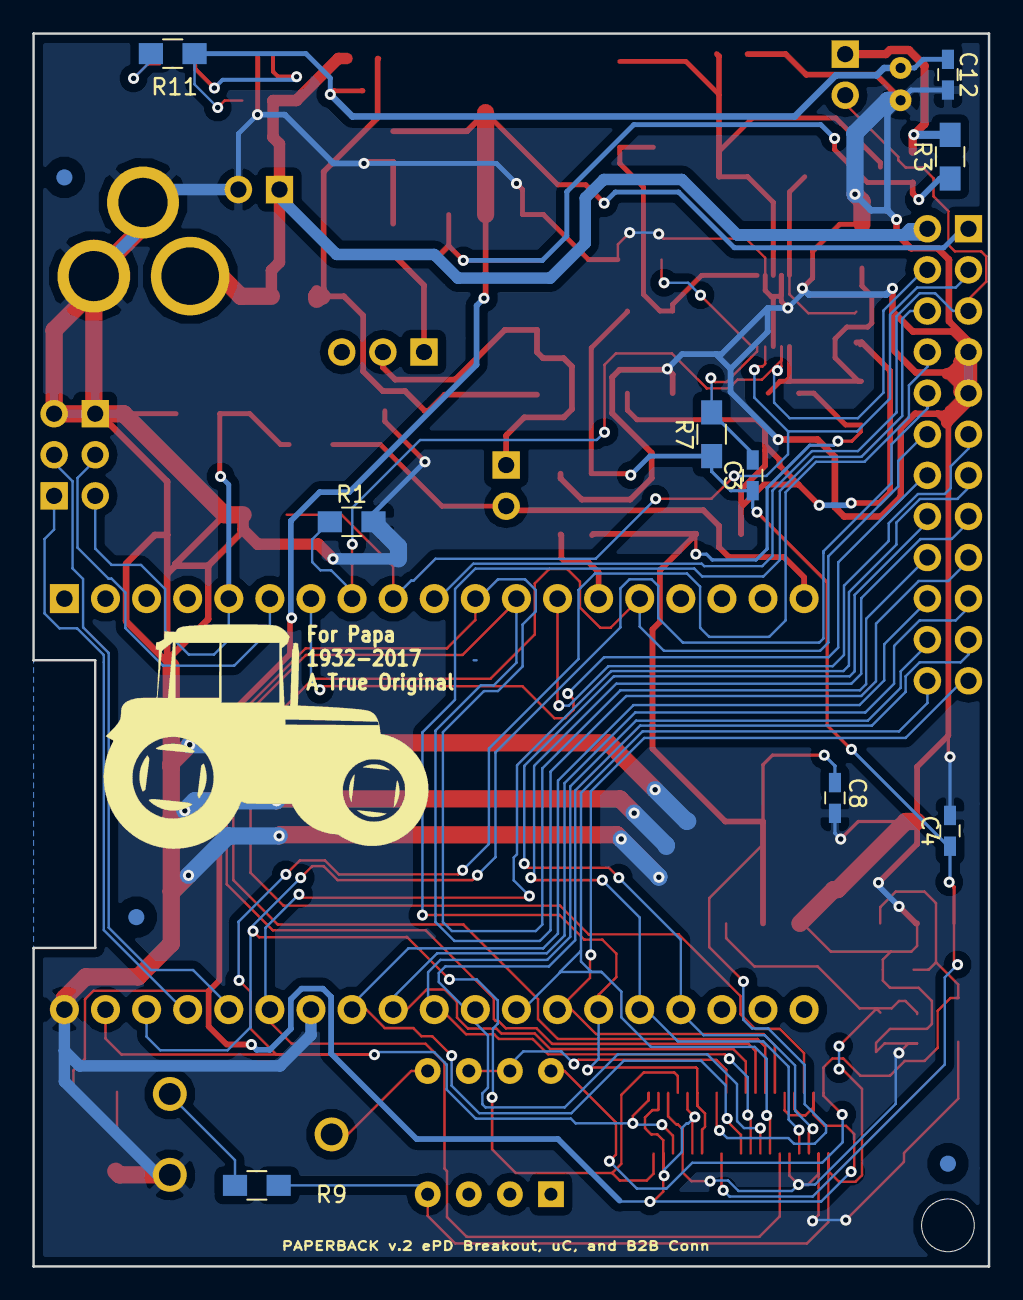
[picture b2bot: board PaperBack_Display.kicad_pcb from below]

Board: 2 copper layers, 59.1 x 76.2 mm, 57 parts (9 on the bottom side), 49 nets.

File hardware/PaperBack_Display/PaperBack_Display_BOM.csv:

Reference, Value, Footprint
U2,MAX1555,TO_SOT_Packages_SMD:SOT-23-5_HandSoldering
D3,LED,LEDs:LED_0805
R11,1K,Resistors_SMD:R_0805_HandSoldering
SINGLE_CELL_LITHIUM1,Battery_Cell,PK_Footprints:JST_Right_Angle_02x01
C12,1uF,Capacitors_SMD:C_0603_HandSoldering
R12,10k,Resistors_SMD:R_0805_HandSoldering
F1,.75A,Resistors_SMD:R_1210_HandSoldering
D5,D_Schottky,PK_Footprints:D_SOD-123F
J2,CONN_01X02,Pin_Headers:Pin_Header_Straight_1x02_Pitch2.54mm
C6,4.7uF,Capacitors_SMD:C_0603_HandSoldering
C7,4.7uF,Capacitors_SMD:C_0603_HandSoldering
L1,22uH,PK_Footprints:DG6050C_Murata_Inductor
L2,22uH,PK_Footprints:DG6050C_Murata_Inductor
C3,4.7pF >22V,Capacitors_SMD:C_0603_HandSoldering
R8,120k >22V,Resistors_SMD:R_0805_HandSoldering
R7,2M >22V,Resistors_SMD:R_0805_HandSoldering
D1,D_Schottky,PK_Footprints:D_SOD-123F
C4,1uF >22V,Capacitors_SMD:C_0603_HandSoldering
U5,LM7915CT,TO_SOT_Packages_SMD:TO-252-3_TabPin2
C10,1uF > 15V,Capacitors_SMD:C_0603_HandSoldering
C8,.33uF > 20V,Capacitors_SMD:C_0603_HandSoldering
U6,LM7815CT,TO_SOT_Packages_SMD:TO-252-3_TabPin2
C9,.33uF > 22V,Capacitors_SMD:C_0603_HandSoldering
C11,1uF > 15V,Capacitors_SMD:C_0603_HandSoldering
R3,10k,Resistors_SMD:R_0805_HandSoldering
R1,10k,Resistors_SMD:R_0805_HandSoldering
R2,10k,Resistors_SMD:R_0805_HandSoldering
U3,LM358,Housings_DIP:DIP-8_W7.62mm
R9,200K,Resistors_SMD:R_0805_HandSoldering
RV1,100k,PK_Footprints:CB10V_Trimmer
R10,39k,Resistors_SMD:R_0805_HandSoldering
R4,39k,Resistors_SMD:R_0805_HandSoldering
JP1,Jumper,Pin_Headers:Pin_Header_Straight_1x02_Pitch2.54mm
J5,CONN_02X12,Pin_Headers:Pin_Header_Straight_2x12_Pitch2.54mm
U7,ESP32_Core_Board_V2,PK_Footprints:ESP32_Core_Board_v2
JP2,Jumper,Pin_Headers:Pin_Header_Straight_1x02_Pitch2.54mm
J4,CONN_01X03,Pin_Headers:Pin_Header_Straight_1x03_Pitch2.54mm
U4,PAM3110BLA330RDICT,TO_SOT_Packages_SMD:TO-252-3_TabPin2
J1,BARREL_JACK,PK_Footprints:Switchcraft_5.5_2.1_Barrel_Jack
R13,1k,Resistors_SMD:R_0805_HandSoldering
D6,LED,LEDs:LED_0805
C13,4.7uF,Capacitors_SMD:C_0603_HandSoldering
U1,LT1945,Housings_SSOP:MSOP-10_3x3mm_Pitch0.5mm
SW1,SW_DPDT_x2,Pin_Headers:Pin_Header_Straight_1x03_Pitch2.54mm
D4,D_Schottky,PK_Footprints:D_SOD-123F
D2,D_Schottky,PK_Footprints:D_SOD-123F
C2,100pF,Capacitors_SMD:C_0603_HandSoldering
R5,560k > 20V,Resistors_SMD:R_0805_HandSoldering
R6,39k > 20V,Resistors_SMD:R_0805_HandSoldering
C5,1uF >20V,Capacitors_SMD:C_0603_HandSoldering
C1,.1uF,Capacitors_SMD:C_0603_HandSoldering
Q1,IRLML6402,TO_SOT_Packages_SMD:SOT-23
Q2,IRLML6402,TO_SOT_Packages_SMD:SOT-23
J6,ED060SC4,PK_Footprints:ED060SC4
J3,CONN_01X03,Pin_Headers:Pin_Header_Straight_1x03_Pitch2.54mm
R15,560k,Resistors_SMD:R_0805_HandSoldering
R14,180k,Resistors_SMD:R_0805_HandSoldering

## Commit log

2017-06-11 Add Python image conversion script
2017-06-11 Logo
2017-06-11 Create README.md
    Add the logo in the Readme
2017-06-11 Initial firmware for ESP32, shows a static image
2017-06-11 Rename
2017-06-11 Better contrast
2017-07-10 Hardware
2017-07-10 Schematic as a PDF
2017-07-10 License and info about hardware
2017-07-10 Update README.md
    Change description
2017-07-10 Firmware update & new PCB image
2017-07-12 Cleaner CSV
2017-07-23 Update Readme.md
    Update Readme for board 2
2017-07-23 Board 2! Don't build yet, let me be the guinea pig. Will update.
2017-07-23 Add schematic
2017-10-08 Adding firmware for second board, UC at first
2017-10-08 VHDL MVP of VGA Display, ~ frame every 5 seconds, can't change it
2017-10-08 Should not have been removed: BOM
2017-10-08 Prose
2017-10-15 New features with the user switch
2017-10-15 Prose and Microcontroller
2017-10-15 Update README.md
    Formatting
2017-12-13 Improve color rendering for 16-bit mode, rewrite Python
